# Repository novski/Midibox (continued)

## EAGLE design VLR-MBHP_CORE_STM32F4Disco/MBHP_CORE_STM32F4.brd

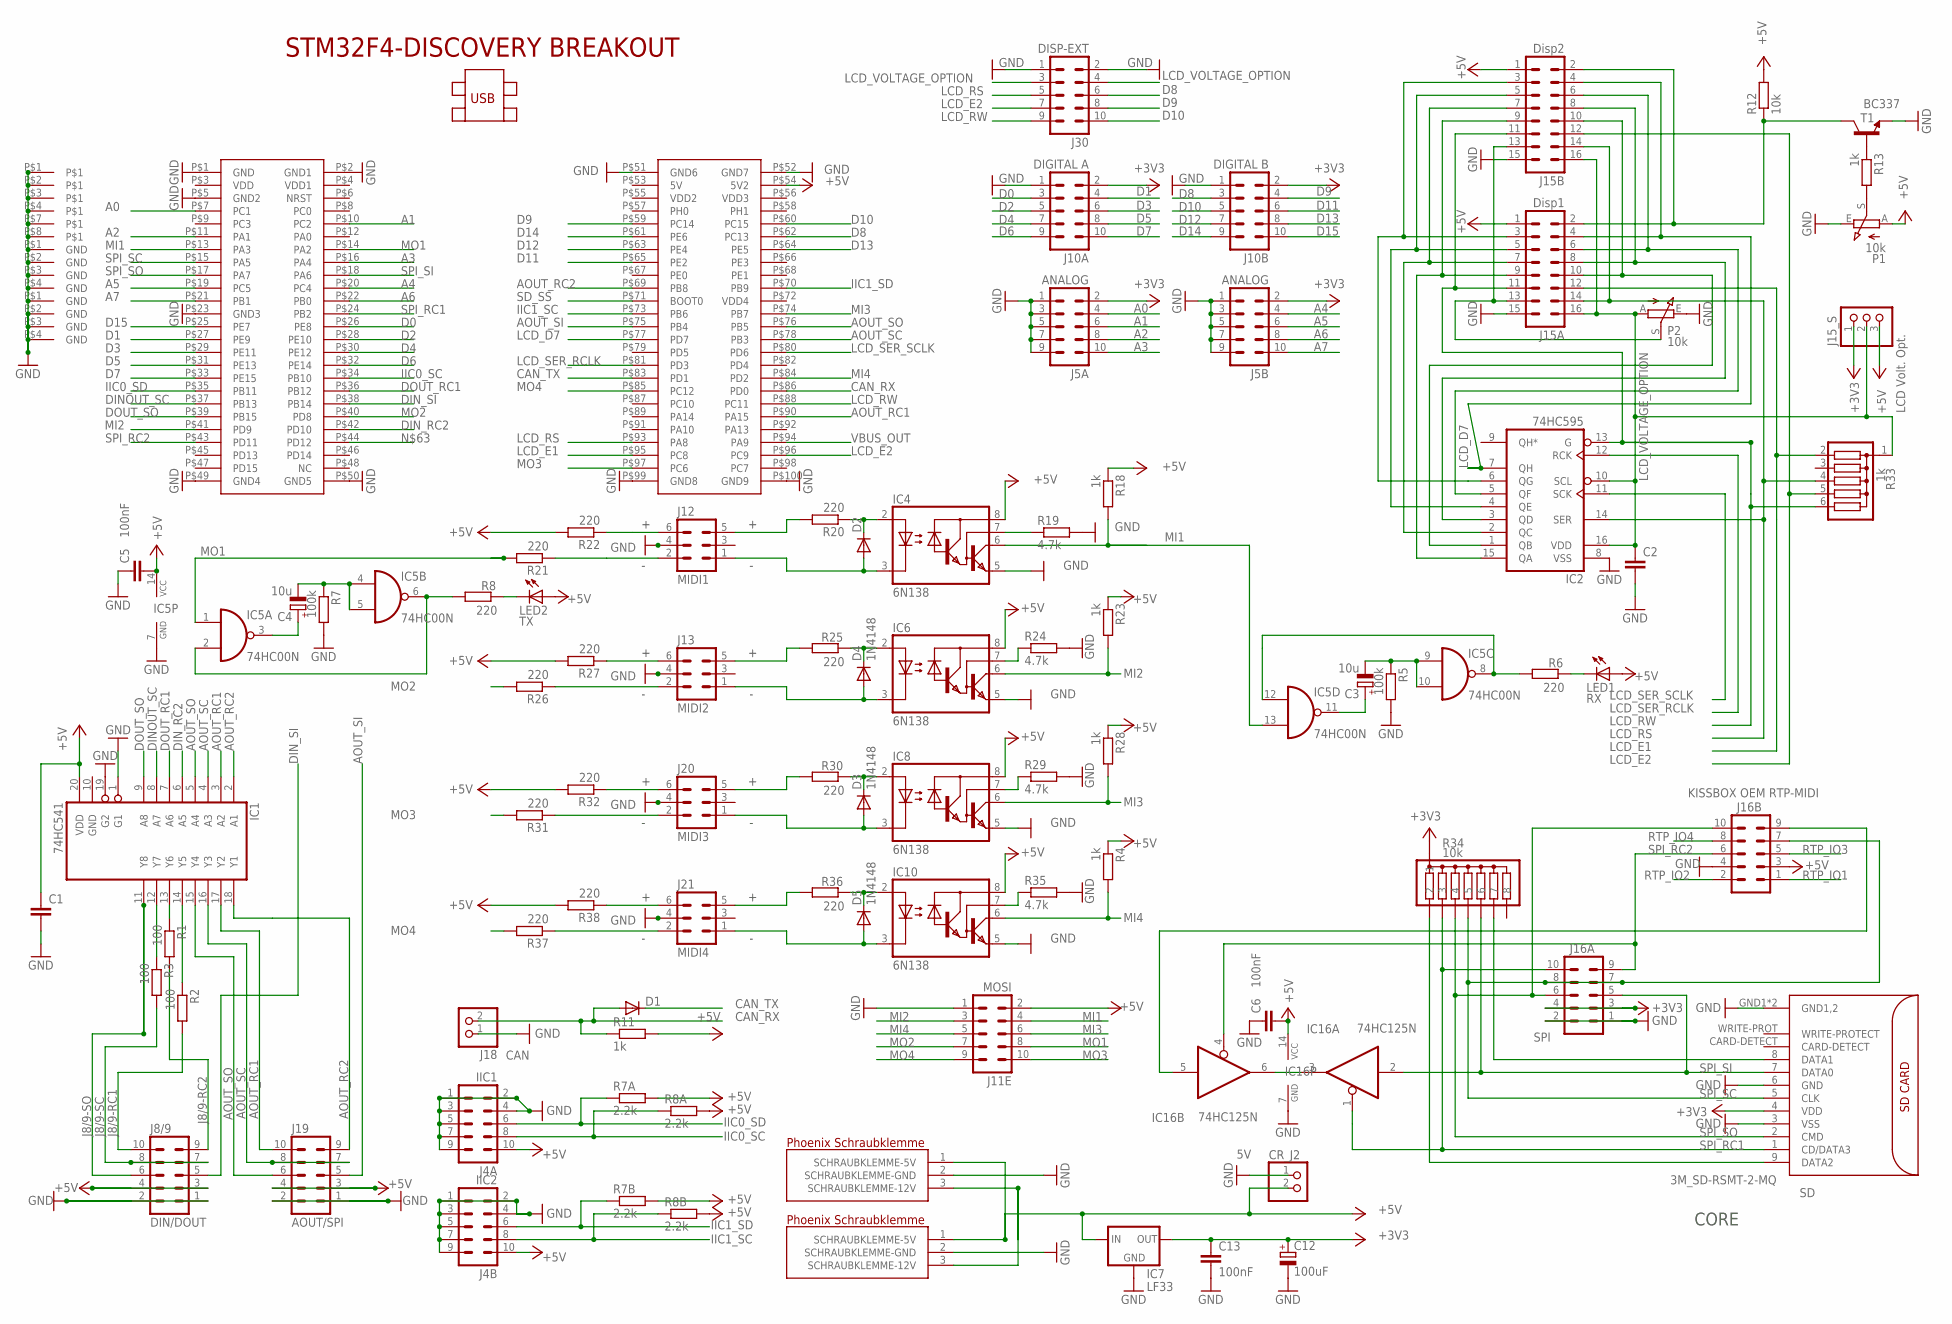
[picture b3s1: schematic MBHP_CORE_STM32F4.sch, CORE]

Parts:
C1, C2: C-EU025-025X050; C025-025X050
C3, C4: 10u; E2,5-6
C5, C6, C13: 100nF; C025-025X050
C12: 100uF; E5-10,5
CR_J2: 5V; 1X02
D1, D3, D4, D5: 1N4148; DO35-7
D2: 1N4148DO35-7; DO35-7
IC1: 74HC541; DIL20
IC2: 74HC595; DIL16
IC4, IC6, IC8, IC10: 6N138; DIL08
IC5: 74HC00N; DIL14
IC7: LF33; TO220
IC16: 74HC125N; DIL14
J1A, J1B: PT-1.5/3; PT-1.5/3-5.0
J4A: IIC1; ML10
J4B: IIC2; ML10
J5A, J5B: ANALOG; ML10
J8/9: DIN/DOUT; ML10
J10A: DIGITAL A; ML10
J10B: DIGITAL B; ML10
J11E: MOSI; ML10
J12: MIDI1; ML6
J13: MIDI2; ML6
J15A: Disp1; ML16
J15B: Disp2; ML16
J15_S: LCD Volt. Opt.; 1X03
J16A: SPI; ML10
J16B: KISSBOX OEM RTP-MIDI; ML10
J18: CAN; 1X02
J19: AOUT/SPI; ML10
J20: MIDI3; ML6
J21: MIDI4; ML6
J30: DISP-EXT; ML10
LED1: RX; LED3MM
LED2: TX; LED3MM
OUTLINE: MIDIBOX_FULL; MIDIBOX14X12
P1, P2: 10k; 6MM_V
R1, R2, R3: 100; 0204/7
R4, R11, R13, R18, R23, R28: 1k; 0204/7
R5, R7: 100k; 0204/7
R6, R8, R20, R21, R22, R25, R26, R27, R30, R31, R32, R36, R37, R38: 220; 0204/7
R7A, R7B, R8A, R8B: 2.2k; 0204/7
R12: 10k; 0204/7
R19, R24, R29, R35: 4.7k; 0204/7
R33: 1k; SIL6
R34: 10k; SIL8
SD: 3M_SD-RSMT-2-MQ
STM32F4DISCOVERY: STM32F4-DISCOVERY
T1: BC337; TO92
U$1, U$2: KEYSTONE_SCREW_TERMINAL

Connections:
+3V3: C12.+, C13.1, IC7.OUT, J5A.2, J5B.2, J10A.2, J10B.2, J15_S.1, J16A.3, J16A.4, R34.1, SD.4 (VDD)
+5V: C1.1, C5.2, C6.2, CR_J2.2, IC1.20 (VDD), IC4.8 (VCC), IC5.14 (VCC), IC6.8 (VCC), IC7.IN, IC8.8 (VCC), IC10.8 (VCC), IC16.14 (VCC), J1A.1 (SCHRAUBKLEMME-5V), J1B.1 (SCHRAUBKLEMME-5V), J4A.10, J4B.10, J8/9.3, J8/9.4, J11E.2, J15A.1, J15B.1, J15_S.3, J16B.3, J19.3, J19.4, LED1.A, LED2.A, P1.A, R4.1, R7A.2, R7B.2, R8A.2, R8B.2, R11.2, R12.2, R18.1, R22.2, R23.1, R27.2, R28.1, R32.2, R38.2, STM32F4DISCOVERY.P$54 (5V2)
+12V1: J1A.3 (SCHRAUBKLEMME-12V), J1B.3 (SCHRAUBKLEMME-12V)
A0: J5A.4, STM32F4DISCOVERY.P$7 (PC1)
A1: J5A.6, STM32F4DISCOVERY.P$10 (PC2)
A2: J5A.8, STM32F4DISCOVERY.P$11 (PA1)
A3: J5A.10, STM32F4DISCOVERY.P$16 (PA4)
A4: J5B.4, STM32F4DISCOVERY.P$20 (PC4)
A5: J5B.6, STM32F4DISCOVERY.P$19 (PC5)
A6: J5B.8, STM32F4DISCOVERY.P$22 (PB0)
A7: J5B.10, STM32F4DISCOVERY.P$21 (PB1)
AOUT_RC1: IC1.3 (A2), IC1.17 (Y2), J19.10, STM32F4DISCOVERY.P$90 (PA15)
AOUT_RC2: IC1.2 (A1), IC1.18 (Y1), J19.9, STM32F4DISCOVERY.P$69 (PB8)
AOUT_SC: IC1.4 (A3), IC1.16 (Y3), J19.7, J19.8, STM32F4DISCOVERY.P$78 (PB3)
AOUT_SI: J19.5, STM32F4DISCOVERY.P$75 (PB4)
AOUT_SO: IC1.5 (A4), IC1.15 (Y4), J19.6, STM32F4DISCOVERY.P$76 (PB5)
CAN_RX: D1.A, J18.2, R11.1, STM32F4DISCOVERY.P$86 (PD0)
CAN_TX: D1.C, STM32F4DISCOVERY.P$83 (PD1)
CR_M1-: D2.A, IC4.3 (C), J12.1
CR_M2+$1: D2.C, IC4.2 (A), R20.1
D0: J10A.3, STM32F4DISCOVERY.P$26 (PE8)
D1: J10A.4, STM32F4DISCOVERY.P$27 (PE9)
D2: J10A.5, STM32F4DISCOVERY.P$28 (PE10)
D3: J10A.6, STM32F4DISCOVERY.P$29 (PE11)
D4: J10A.7, STM32F4DISCOVERY.P$30 (PE12)
D5: J10A.8, STM32F4DISCOVERY.P$31 (PE13)
D6: J10A.9, STM32F4DISCOVERY.P$32 (PE14)
D7: J10A.10, STM32F4DISCOVERY.P$33 (PE15)
D8: J10B.3, J30.6, STM32F4DISCOVERY.P$62 (PC13)
D9: J10B.4, J30.8, STM32F4DISCOVERY.P$59 (PC14)
D10: J10B.5, J30.10, STM32F4DISCOVERY.P$60 (PC15)
D11: J10B.6, STM32F4DISCOVERY.P$65 (PE2)
D12: J10B.7, STM32F4DISCOVERY.P$63 (PE4)
D13: J10B.8, STM32F4DISCOVERY.P$64 (PE5)
D14: J10B.9, STM32F4DISCOVERY.P$61 (PE6)
D15: J10B.10, STM32F4DISCOVERY.P$25 (PE7)
DINOUT_SC: IC1.8 (A7), STM32F4DISCOVERY.P$37 (PB13)
DIN_RC2: IC1.6 (A5), STM32F4DISCOVERY.P$42 (PD10)
DIN_SI: J8/9.5, STM32F4DISCOVERY.P$38 (PB14)
DOUT_RC1: IC1.7 (A6), STM32F4DISCOVERY.P$36 (PB12)
DOUT_SO: IC1.9 (A8), STM32F4DISCOVERY.P$39 (PB15)
GND: C1.2, C2.2, C5.1, C6.1, C12.-, C13.2, CR_J2.1, IC1.1 (G1), IC1.10 (GND), IC1.19 (G2), IC2.8 (VSS), IC4.5 (GND), IC5.7 (GND), IC6.5 (GND), IC7.GND, IC8.5 (GND), IC10.5 (GND), IC16.7 (GND), J1A.2 (SCHRAUBKLEMME-GND), J1B.2 (SCHRAUBKLEMME-GND), J4A.1, J4A.2, J4A.3, J4A.4, J4A.5, J4A.7, J4A.9, J4B.1, J4B.2, J4B.3, J4B.4, J4B.5, J4B.7, J4B.9, J5A.1, J5A.3, J5A.5, J5A.7, J5A.9, J5B.1, J5B.3, J5B.5, J5B.7, J5B.9, J8/9.1, J8/9.2, J10A.1, J10B.1, J11E.1, J12.4, J13.4, J15A.15, J15B.15, J16A.1, J16A.2, J16B.4, J18.1, J19.1, J19.2, J20.4, J21.4, J30.1, J30.2, OUTLINE.P$1, OUTLINE.P$2, OUTLINE.P$3, OUTLINE.P$4, OUTLINE.P$7, OUTLINE.P$8, P1.E, P2.E, R5.2, R7.2, R19.2, R24.2, R29.2, R35.2, SD.3 (VSS), SD.6 (GND), SD.GND1 (GND1,2), SD.GND2 (GND1,2), STM32F4DISCOVERY.P$1 (GND), STM32F4DISCOVERY.P$2 (GND1), STM32F4DISCOVERY.P$5 (GND2), STM32F4DISCOVERY.P$23 (GND3), STM32F4DISCOVERY.P$49 (GND4), STM32F4DISCOVERY.P$50 (GND5), STM32F4DISCOVERY.P$51 (GND6), STM32F4DISCOVERY.P$52 (GND7), STM32F4DISCOVERY.P$99 (GND8), STM32F4DISCOVERY.P$100 (GND9), T1.1 (E), U$1.P$1, U$1.P$2, U$1.P$3, U$1.P$4, U$2.P$1, U$2.P$2, U$2.P$3, U$2.P$4
IIC0_SC: J4A.8, R8A.1, STM32F4DISCOVERY.P$34 (PB10)
IIC0_SD: J4A.6, R7A.1, STM32F4DISCOVERY.P$35 (PB11)
IIC1_SC: J4B.8, R8B.1, STM32F4DISCOVERY.P$73 (PB6)
IIC1_SD: J4B.6, R7B.1, STM32F4DISCOVERY.P$70 (PB9)
J8/9-RC1: J8/9.10, R2.2
J8/9-RC2: J8/9.9, R1.2
J8/9-SC: J8/9.7, J8/9.8, R3.2
J8/9-SO: IC1.11 (Y8), J8/9.6
LCD_D7: IC2.7 (QH), J15A.4, J15B.4, STM32F4DISCOVERY.P$77 (PD7)
LCD_E1: J15A.12, R33.2, STM32F4DISCOVERY.P$95 (PC8)
LCD_E2: J15B.12, J30.7, R33.5, STM32F4DISCOVERY.P$96 (PC9)
LCD_RS: IC2.14 (SER), J15A.14, J15B.14, J30.5, R33.4, STM32F4DISCOVERY.P$93 (PA8)
LCD_RW: IC2.13 (G), J15A.11, J15B.11, J30.9, R33.6, STM32F4DISCOVERY.P$88 (PC11)
LCD_SER_RCLK: IC2.12 (RCK), STM32F4DISCOVERY.P$81 (PD3)
LCD_SER_SCLK: IC2.11 (SCK), STM32F4DISCOVERY.P$80 (PD6)
LCD_VOLTAGE_OPTION: C2.1, IC2.10 (SCL), IC2.16 (VDD), J15A.16, J15B.16, J15_S.2, J30.3, J30.4, P2.A, R33.1
MF_M+ZULEITUNG: J13.5, R25.2
MF_M+ZULEITUNG1: J20.5, R30.2
MF_M+ZULEITUNG2: J21.5, R36.2
MF_M-ZULEITUNG: D4.A, IC6.3 (C), J13.1
MF_M-ZULEITUNG1: D3.A, IC8.3 (C), J20.1
MF_M-ZULEITUNG2: D5.A, IC10.3 (C), J21.1
MI1: IC4.6 (VO), IC5.13 (I1), J11E.4, R18.2, STM32F4DISCOVERY.P$13 (PA3)
MI2: IC6.6 (VO), J11E.3, R23.2, STM32F4DISCOVERY.P$41 (PD9)
MI3: IC8.6 (VO), J11E.6, R28.2, STM32F4DISCOVERY.P$74 (PB7)
MI4: IC10.6 (VO), J11E.5, R4.2, STM32F4DISCOVERY.P$84 (PD2)
MO1: IC5.1 (I0), J11E.8, R21.2, STM32F4DISCOVERY.P$14 (PA2)
MO2: J11E.7, R26.2, STM32F4DISCOVERY.P$40 (PD8)
MO3: J11E.10, R31.2, STM32F4DISCOVERY.P$97 (PC6)
MO4: J11E.9, R37.2, STM32F4DISCOVERY.P$85 (PC12)
unnamed: IC2.6 (QG), J15A.3, J15B.3
unnamed: IC2.5 (QF), J15A.6, J15B.6
unnamed: IC2.4 (QE), J15A.5, J15B.5
unnamed: IC2.3 (QD), J15A.8, J15B.8
unnamed: R34.2, SD.9 (DATA2)
unnamed: IC16.5 (I), J16B.9
unnamed: R34.7, SD.8 (DATA1)
unnamed: IC2.2 (QC), J15A.7, J15B.7
unnamed: IC2.1 (QB), J15A.10, J15B.10
unnamed: IC2.15 (QA), J15A.9, J15B.9
unnamed: IC4.7 (VB), R19.1
unnamed: J15A.13, J15B.13, P2.S
unnamed: IC16.3 (O), IC16.6 (O)
unnamed: P1.S, R13.2
unnamed: R13.1, T1.2 (B)
unnamed: J12.6, R22.1
unnamed: J15A.2, J15B.2, R12.1, T1.3 (C)
unnamed: D4.C, IC6.2 (A), R25.1
unnamed: J12.5, R20.2
unnamed: C3.-, IC5.9 (I0), IC5.10 (I1), R5.1
unnamed: C3.+, IC5.11 (O)
unnamed: IC5.8 (O), IC5.12 (I0), R6.2
unnamed: J13.6, R27.1
unnamed: J13.2, R26.1
unnamed: LED1.K (C), R6.1
unnamed: D3.C, IC8.2 (A), R30.1
unnamed: IC8.7 (VB), R29.1
unnamed: J20.6, R32.1
unnamed: J20.2, R31.1
unnamed: D5.C, IC10.2 (A), R36.1
unnamed: IC10.7 (VB), R35.1
unnamed: J21.6, R38.1
unnamed: J21.2, R37.1
unnamed: IC5.4 (I0), IC5.5 (I1)
unnamed: C4.-, R7.1
unnamed: C4.+, IC5.3 (O)
unnamed: IC5.2 (I1), IC5.6 (O), R8.2
unnamed: LED2.K (C), R8.1
unnamed: J12.2, R21.1
unnamed: IC6.7 (VB), R24.1
RC-I-: IC1.14 (Y5), R2.1
RC-O-: IC1.13 (Y6), R1.1
RTP_IO1: J16B.1
RTP_IO2: J16B.2
RTP_IO3: J16B.5
RTP_IO4: J16B.8
SC-: IC1.12 (Y7), R3.1
SD_SS: STM32F4DISCOVERY.P$71 (BOOT0)
SPI_RC1: IC16.1 (OE), J16A.10, R34.3, SD.1 (CD/DATA3), STM32F4DISCOVERY.P$24 (PB2)
SPI_RC2: IC16.4 (OE), J16A.9, J16B.6, STM32F4DISCOVERY.P$43 (PD11)
SPI_SC: J16A.7, J16A.8, J16B.7, R34.5, SD.5 (CLK), STM32F4DISCOVERY.P$15 (PA5)
SPI_SI: IC16.2 (I), J16A.5, R34.6, SD.7 (DATA0), STM32F4DISCOVERY.P$18 (PA6)
SPI_SO: J16A.6, J16B.10, R34.4, SD.2 (CMD), STM32F4DISCOVERY.P$17 (PA7)
VBUS_OUT: STM32F4DISCOVERY.P$94 (PA9)

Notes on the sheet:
CORE

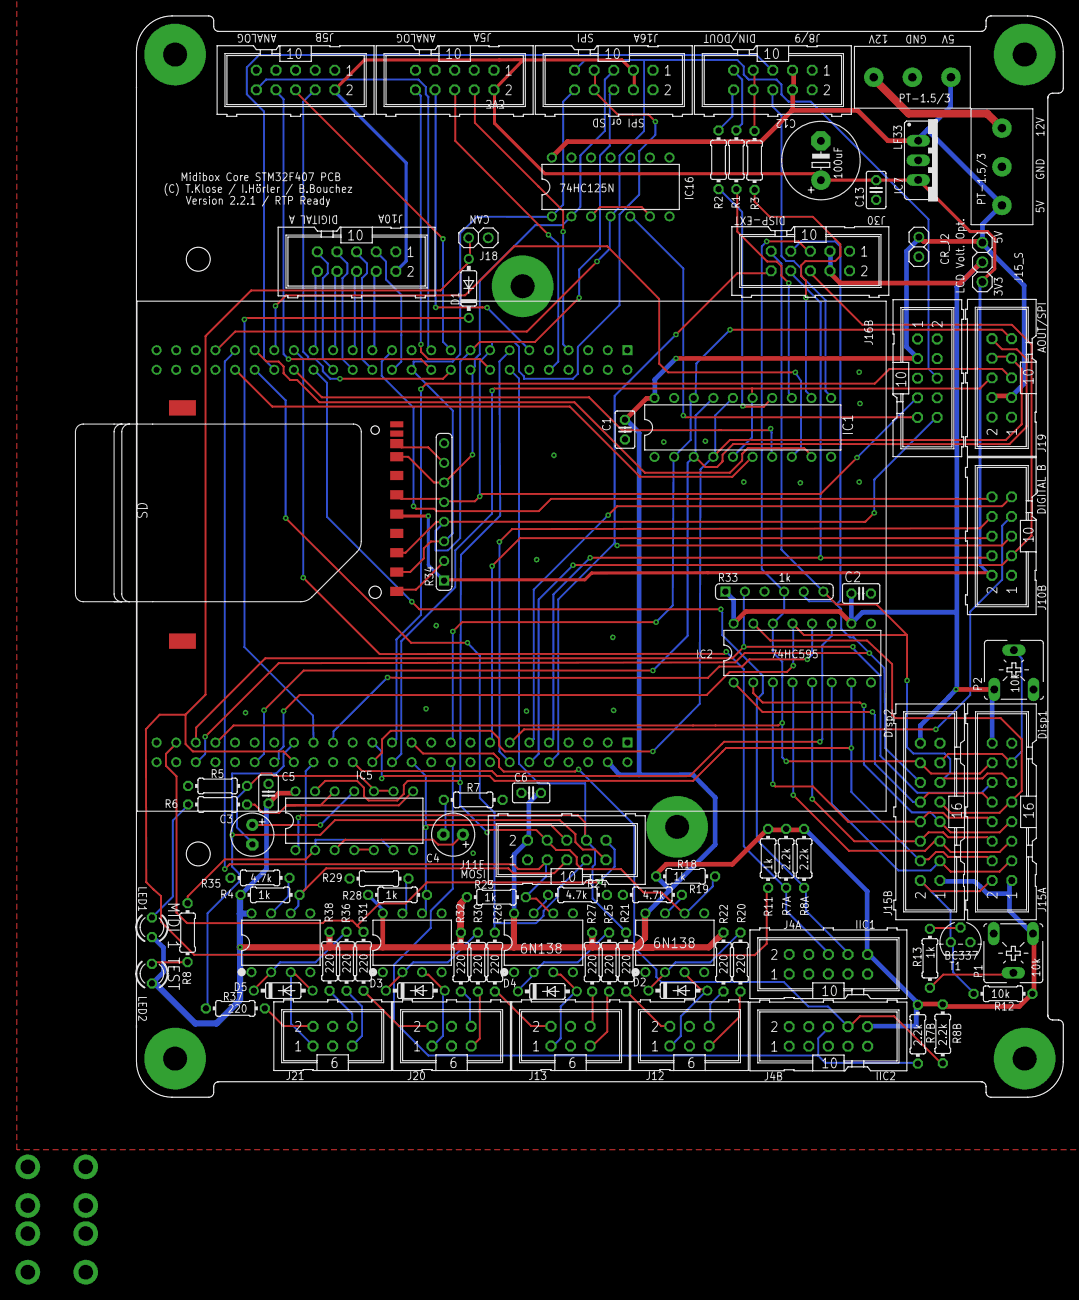
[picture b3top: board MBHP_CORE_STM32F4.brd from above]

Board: 2 copper layers, 120.0 x 140.0 mm, 93 parts (1 on the bottom side), 120 nets.

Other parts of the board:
U$6, U$7: VLRLAB

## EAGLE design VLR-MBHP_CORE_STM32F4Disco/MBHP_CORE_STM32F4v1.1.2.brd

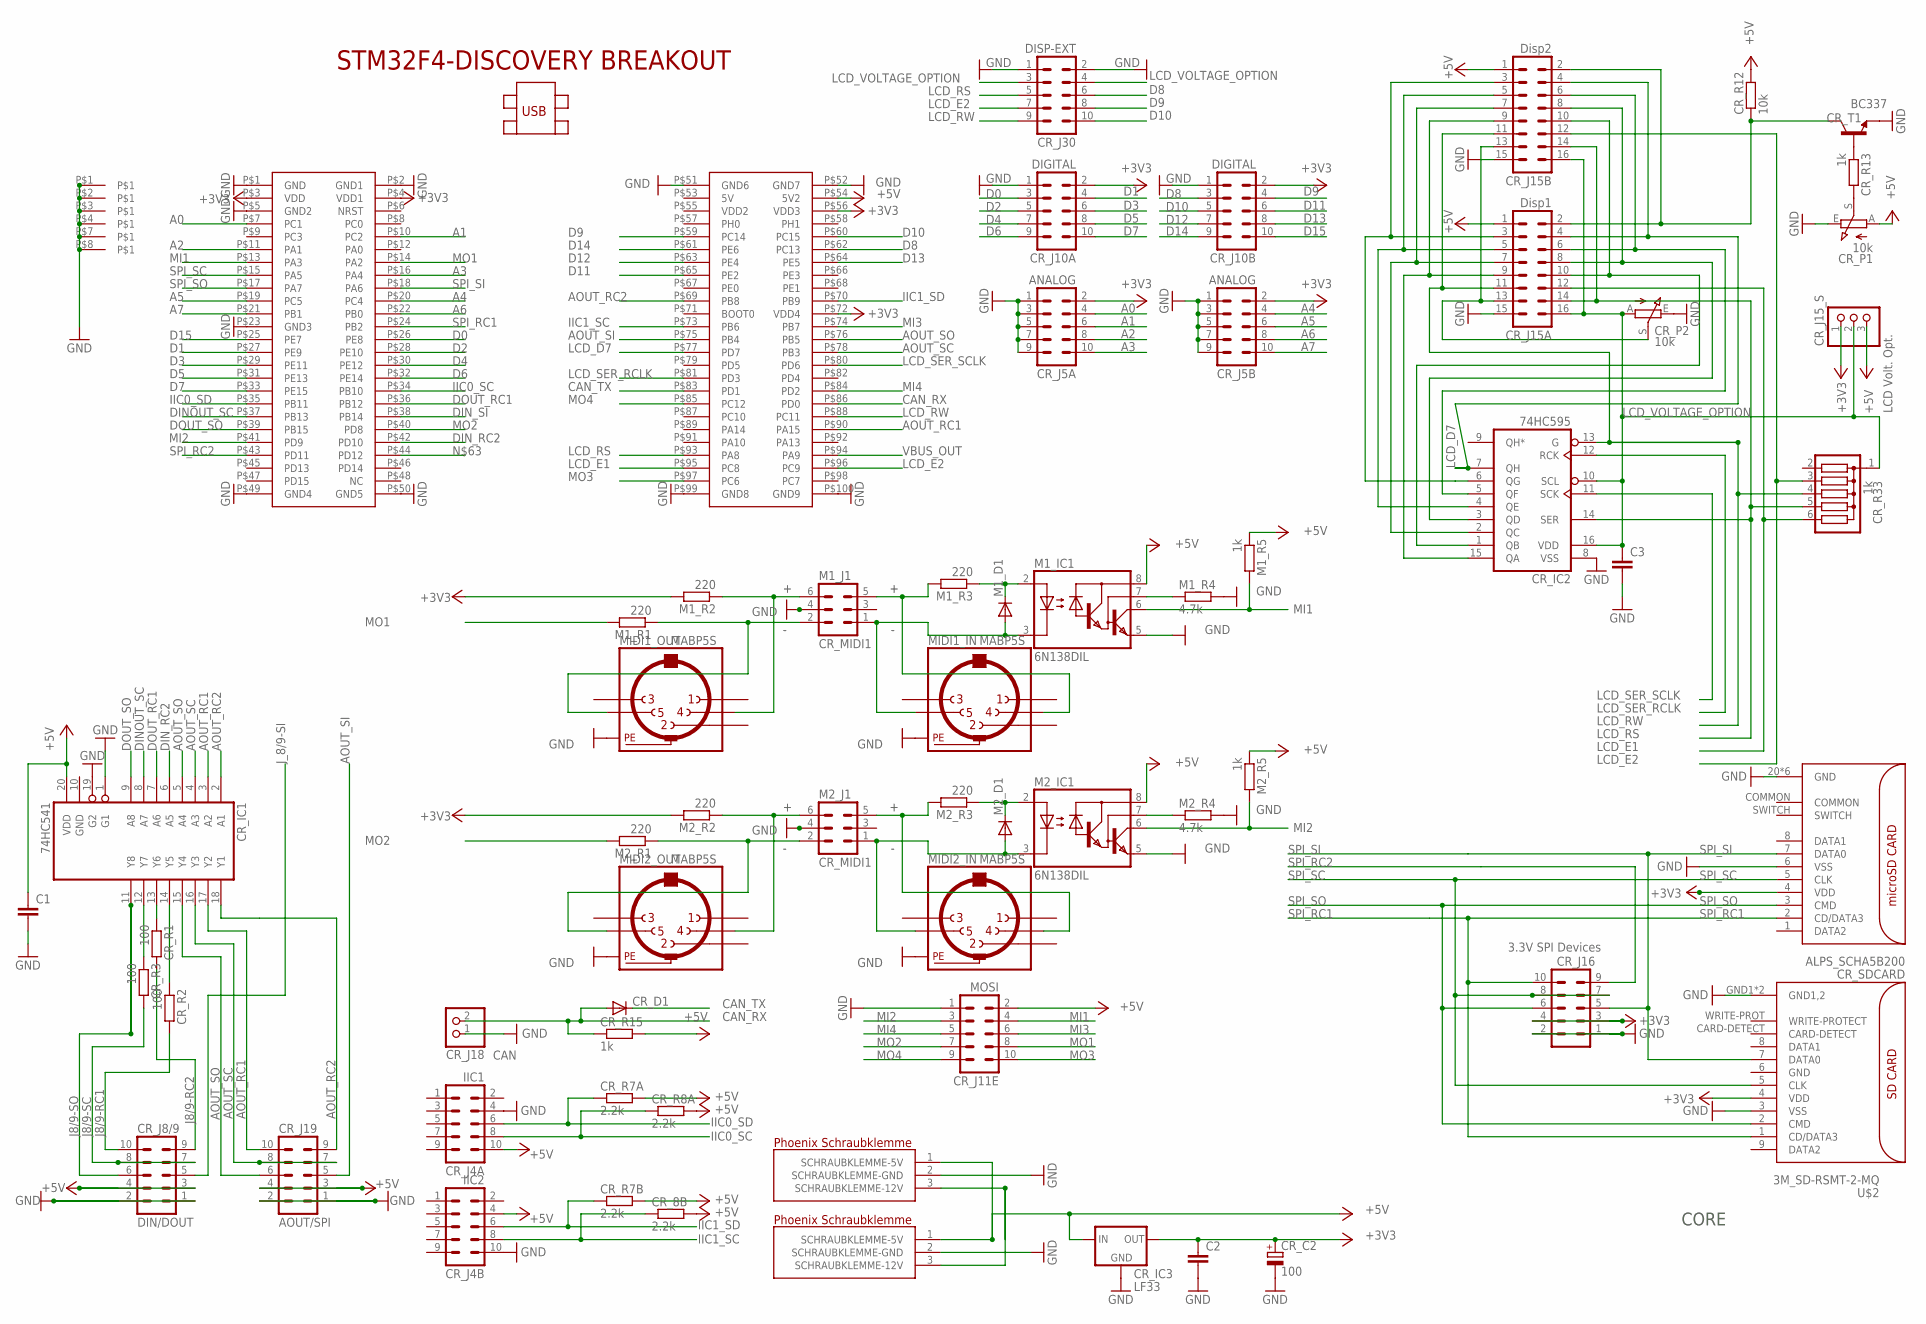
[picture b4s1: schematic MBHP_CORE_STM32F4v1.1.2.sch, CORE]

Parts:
C1, C2, C3: C-EU025-025X050; C025-025X050
CR_8B: 2.2k; 0204/7
CR_C2: 100; E5-10,5
CR_D1: 1N4148; DO35-7
CR_IC1: 74HC541; DIL20
CR_IC2: 74HC595; DIL16
CR_IC3: LF33; TO220
CR_J4A: IIC1; ML10
CR_J4B: IIC2; ML10
CR_J5A, CR_J5B: ANALOG; ML10
CR_J8/9: DIN/DOUT; ML10
CR_J10A, CR_J10B: DIGITAL; ML10
CR_J11E: MOSI; ML10
CR_J15A: Disp1; ML16
CR_J15B: Disp2; ML16
CR_J15_S: LCD Volt. Opt.; 1X03
CR_J16: 3.3V SPI Devices; ML10
CR_J18: CAN; 1X02
CR_J19: AOUT/SPI; ML10
CR_J30: DISP-EXT; ML10
CR_P1, CR_P2: 10k; 6MM_V
CR_R1, CR_R2, CR_R3: 100; 0204/7
CR_R7A, CR_R7B, CR_R8A: 2.2k; 0204/7
CR_R12: 10k; 0204/7
CR_R13, CR_R15: 1k; 0204/7
CR_R33: 1k; SIL6
CR_SDCARD: ALPS_SCHA5B200; ALPS_SCHA5B0200_MICRO_SD_PUSHPUSH
CR_T1: BC337; TO92
KLEMME3, KLEMME4: PT-1.5/3; PT-1.5/3-5.0
M1_D1, M2_D1: 1N4148DO35-7; DO35-7
M1_IC1, M2_IC1: 6N138DIL; DIL08
M1_J1, M2_J1: CR_MIDI1; ML6
M1_R1, M1_R2, M1_R3, M2_R1, M2_R2, M2_R3: 220; 0204/7
M1_R4, M2_R4: 4.7k; 0204/7
M1_R5, M2_R5: 1k; 0204/7
MIDI1_IN, MIDI1_OUT, MIDI2_IN, MIDI2_OUT: MABP5S
OUTLINE: MIDIBOX_FULL; MIDIBOX14X12
STM32F4DISCOVERY: STM32F4-DISCOVERY
U$2: 3M_SD-RSMT-2-MQ

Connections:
+3V3: C2.1, CR_C2.+, CR_IC3.OUT, CR_J5A.2, CR_J5B.2, CR_J10A.2, CR_J10B.2, CR_J15_S.1, CR_J16.3, CR_J16.4, CR_SDCARD.4 (VDD), M1_R2.2, M2_R2.2, STM32F4DISCOVERY.P$3 (VDD), STM32F4DISCOVERY.P$4 (VDD1), STM32F4DISCOVERY.P$56 (VDD3), STM32F4DISCOVERY.P$72 (VDD4), U$2.4 (VDD)
+5V: C1.1, CR_8B.2, CR_IC1.20 (VDD), CR_IC3.IN, CR_J4A.10, CR_J4B.4, CR_J8/9.3, CR_J8/9.4, CR_J11E.2, CR_J15A.1, CR_J15B.1, CR_J15_S.3, CR_J19.3, CR_J19.4, CR_P1.A, CR_R7A.2, CR_R7B.2, CR_R8A.2, CR_R12.2, CR_R15.2, KLEMME3.1 (SCHRAUBKLEMME-5V), KLEMME4.1 (SCHRAUBKLEMME-5V), M1_IC1.8 (VCC), M1_R5.1, M2_IC1.8 (VCC), M2_R5.1, STM32F4DISCOVERY.P$54 (5V2)
+12V1: KLEMME3.3 (SCHRAUBKLEMME-12V), KLEMME4.3 (SCHRAUBKLEMME-12V)
A0: CR_J5A.4, STM32F4DISCOVERY.P$7 (PC1)
A1: CR_J5A.6, STM32F4DISCOVERY.P$10 (PC2)
A2: CR_J5A.8, STM32F4DISCOVERY.P$11 (PA1)
A3: CR_J5A.10, STM32F4DISCOVERY.P$16 (PA4)
A4: CR_J5B.4, STM32F4DISCOVERY.P$20 (PC4)
A5: CR_J5B.6, STM32F4DISCOVERY.P$19 (PC5)
A6: CR_J5B.8, STM32F4DISCOVERY.P$22 (PB0)
A7: CR_J5B.10, STM32F4DISCOVERY.P$21 (PB1)
AOUT_RC1: CR_IC1.3 (A2), CR_IC1.17 (Y2), CR_J19.10, STM32F4DISCOVERY.P$90 (PA15)
AOUT_RC2: CR_IC1.2 (A1), CR_IC1.18 (Y1), CR_J19.9, STM32F4DISCOVERY.P$69 (PB8)
AOUT_SC: CR_IC1.4 (A3), CR_IC1.16 (Y3), CR_J19.7, CR_J19.8, STM32F4DISCOVERY.P$78 (PB3)
AOUT_SI: CR_J19.5, STM32F4DISCOVERY.P$75 (PB4)
AOUT_SO: CR_IC1.5 (A4), CR_IC1.15 (Y4), CR_J19.6, STM32F4DISCOVERY.P$76 (PB5)
CAN_RX: CR_D1.A, CR_J18.2, CR_R15.1, STM32F4DISCOVERY.P$86 (PD0)
CAN_TX: CR_D1.C, STM32F4DISCOVERY.P$83 (PD1)
D0: CR_J10A.3, STM32F4DISCOVERY.P$26 (PE8)
D1: CR_J10A.4, STM32F4DISCOVERY.P$27 (PE9)
D2: CR_J10A.5, STM32F4DISCOVERY.P$28 (PE10)
D3: CR_J10A.6, STM32F4DISCOVERY.P$29 (PE11)
D4: CR_J10A.7, STM32F4DISCOVERY.P$30 (PE12)
D5: CR_J10A.8, STM32F4DISCOVERY.P$31 (PE13)
D6: CR_J10A.9, STM32F4DISCOVERY.P$32 (PE14)
D7: CR_J10A.10, STM32F4DISCOVERY.P$33 (PE15)
D8: CR_J10B.3, CR_J30.6, STM32F4DISCOVERY.P$62 (PC13)
D9: CR_J10B.4, CR_J30.8, STM32F4DISCOVERY.P$59 (PC14)
D10: CR_J10B.5, CR_J30.10, STM32F4DISCOVERY.P$60 (PC15)
D11: CR_J10B.6, STM32F4DISCOVERY.P$65 (PE2)
D12: CR_J10B.7, STM32F4DISCOVERY.P$63 (PE4)
D13: CR_J10B.8, STM32F4DISCOVERY.P$64 (PE5)
D14: CR_J10B.9, STM32F4DISCOVERY.P$61 (PE6)
D15: CR_J10B.10, STM32F4DISCOVERY.P$25 (PE7)
DINOUT_SC: CR_IC1.8 (A7), STM32F4DISCOVERY.P$37 (PB13)
DIN_RC2: CR_IC1.6 (A5), STM32F4DISCOVERY.P$42 (PD10)
DIN_SI: STM32F4DISCOVERY.P$38 (PB14)
DOUT_RC1: CR_IC1.7 (A6), STM32F4DISCOVERY.P$36 (PB12)
DOUT_SO: CR_IC1.9 (A8), STM32F4DISCOVERY.P$39 (PB15)
GND: C1.2, C2.2, C3.2, CR_C2.-, CR_IC1.1 (G1), CR_IC1.10 (GND), CR_IC1.19 (G2), CR_IC2.8 (VSS), CR_IC3.GND, CR_J4A.4, CR_J4B.10, CR_J5A.1, CR_J5A.3, CR_J5A.5, CR_J5A.7, CR_J5A.9, CR_J5B.1, CR_J5B.3, CR_J5B.5, CR_J5B.7, CR_J5B.9, CR_J8/9.1, CR_J8/9.2, CR_J10A.1, CR_J10B.1, CR_J11E.1, CR_J15A.15, CR_J15B.15, CR_J16.1, CR_J16.2, CR_J18.1, CR_J19.1, CR_J19.2, CR_J30.1, CR_J30.2, CR_P1.E, CR_P2.E, CR_SDCARD.6 (VSS), CR_SDCARD.20 (GND), CR_SDCARD.21 (GND), CR_SDCARD.22 (GND), CR_SDCARD.23 (GND), CR_SDCARD.24 (GND), CR_SDCARD.25 (GND), CR_T1.1 (E), KLEMME3.2 (SCHRAUBKLEMME-GND), KLEMME4.2 (SCHRAUBKLEMME-GND), M1_IC1.5 (GND), M1_J1.4, M1_R4.2, M2_IC1.5 (GND), M2_J1.4, M2_R4.2, MIDI1_IN.PE, MIDI1_IN.PE@ (PE), MIDI1_OUT.PE, MIDI1_OUT.PE@ (PE), MIDI2_IN.PE, MIDI2_IN.PE@ (PE), MIDI2_OUT.PE, MIDI2_OUT.PE@ (PE), OUTLINE.P$1, OUTLINE.P$2, OUTLINE.P$3, OUTLINE.P$4, OUTLINE.P$7, OUTLINE.P$8, STM32F4DISCOVERY.P$1 (GND), STM32F4DISCOVERY.P$2 (GND1), STM32F4DISCOVERY.P$5 (GND2), STM32F4DISCOVERY.P$23 (GND3), STM32F4DISCOVERY.P$49 (GND4), STM32F4DISCOVERY.P$50 (GND5), STM32F4DISCOVERY.P$51 (GND6), STM32F4DISCOVERY.P$52 (GND7), STM32F4DISCOVERY.P$99 (GND8), STM32F4DISCOVERY.P$100 (GND9), U$2.3 (VSS), U$2.GND1 (GND1,2), U$2.GND2 (GND1,2)
IIC0_SC: CR_J4A.8, CR_R8A.1, STM32F4DISCOVERY.P$34 (PB10)
IIC0_SD: CR_J4A.6, CR_R7A.1, STM32F4DISCOVERY.P$35 (PB11)
IIC1_SC: CR_8B.1, CR_J4B.8, STM32F4DISCOVERY.P$73 (PB6)
IIC1_SD: CR_J4B.6, CR_R7B.1, STM32F4DISCOVERY.P$70 (PB9)
J8/9-RC1: CR_J8/9.10, CR_R2.2
J8/9-RC2: CR_J8/9.9, CR_R1.2
J8/9-SC: CR_J8/9.7, CR_J8/9.8, CR_R3.2
J8/9-SO: CR_IC1.11 (Y8), CR_J8/9.6
J_8/9-SI: CR_J8/9.5
LCD_D7: CR_IC2.7 (QH), CR_J15A.4, CR_J15B.4, STM32F4DISCOVERY.P$77 (PD7)
LCD_E1: CR_J15A.12, CR_R33.6, STM32F4DISCOVERY.P$95 (PC8)
LCD_E2: CR_J15B.12, CR_J30.7, CR_R33.3, STM32F4DISCOVERY.P$96 (PC9)
LCD_RS: CR_IC2.14 (SER), CR_J15A.14, CR_J15B.14, CR_J30.5, CR_R33.5, STM32F4DISCOVERY.P$93 (PA8)
LCD_RW: CR_IC2.13 (G), CR_J15A.11, CR_J15B.11, CR_J30.9, CR_R33.4, STM32F4DISCOVERY.P$88 (PC11)
LCD_SER_RCLK: CR_IC2.12 (RCK), STM32F4DISCOVERY.P$81 (PD3)
LCD_SER_SCLK: CR_IC2.11 (SCK), STM32F4DISCOVERY.P$80 (PD6)
LCD_VOLTAGE_OPTION: C3.1, CR_IC2.10 (SCL), CR_IC2.16 (VDD), CR_J15A.16, CR_J15B.16, CR_J15_S.2, CR_J30.3, CR_J30.4, CR_P2.A, CR_R33.1
M1_R4: M1_IC1.7 (VB), M1_R4.1
M1_RX+: M1_J1.5, M1_R3.2, MIDI1_IN.4
M1_RX+D1: M1_D1.C, M1_IC1.2 (A), M1_R3.1
M1_RX-: M1_D1.A, M1_IC1.3 (C), M1_J1.1, MIDI1_IN.5
M1_TX+: M1_J1.6, M1_R2.1, MIDI1_OUT.4
M1_TX-: M1_J1.2, M1_R1.1, MIDI1_OUT.5
M2_R4: M2_IC1.7 (VB), M2_R4.1
M2_RX+: M2_J1.5, M2_R3.2, MIDI2_IN.4
M2_RX+D1: M2_D1.C, M2_IC1.2 (A), M2_R3.1
M2_RX-: M2_D1.A, M2_IC1.3 (C), M2_J1.1, MIDI2_IN.5
M2_TX+: M2_J1.6, M2_R2.1, MIDI2_OUT.4
M2_TX-: M2_J1.2, M2_R1.1, MIDI2_OUT.5
MI1: CR_J11E.4, M1_IC1.6 (VO), M1_R5.2, STM32F4DISCOVERY.P$13 (PA3)
MI2: CR_J11E.3, M2_IC1.6 (VO), M2_R5.2, STM32F4DISCOVERY.P$41 (PD9)
MI3: CR_J11E.6, STM32F4DISCOVERY.P$74 (PB7)
MI4: CR_J11E.5, STM32F4DISCOVERY.P$84 (PD2)
MO1: CR_J11E.8, M1_R1.2, STM32F4DISCOVERY.P$14 (PA2)
MO2: CR_J11E.7, M2_R1.2, STM32F4DISCOVERY.P$40 (PD8)
MO3: CR_J11E.10, STM32F4DISCOVERY.P$97 (PC6)
MO4: CR_J11E.9, STM32F4DISCOVERY.P$85 (PC12)
unnamed: CR_IC2.6 (QG), CR_J15A.3, CR_J15B.3
unnamed: CR_IC2.5 (QF), CR_J15A.6, CR_J15B.6
unnamed: CR_IC2.4 (QE), CR_J15A.5, CR_J15B.5
unnamed: CR_IC2.3 (QD), CR_J15A.8, CR_J15B.8
unnamed: CR_IC2.2 (QC), CR_J15A.7, CR_J15B.7
unnamed: CR_IC2.1 (QB), CR_J15A.10, CR_J15B.10
unnamed: CR_IC2.15 (QA), CR_J15A.9, CR_J15B.9
unnamed: CR_J15A.13, CR_J15B.13, CR_P2.S
unnamed: CR_P1.S, CR_R13.2
unnamed: CR_R13.1, CR_T1.2 (B)
unnamed: CR_J15A.2, CR_J15B.2, CR_R12.1, CR_T1.3 (C)
RC-I-: CR_IC1.14 (Y5), CR_R2.1
RC-O-: CR_IC1.13 (Y6), CR_R1.1
SC-: CR_IC1.12 (Y7), CR_R3.1
SPI_RC1: CR_J16.10, CR_SDCARD.2 (CD/DATA3), STM32F4DISCOVERY.P$24 (PB2), U$2.1 (CD/DATA3)
SPI_RC2: CR_J16.9, STM32F4DISCOVERY.P$43 (PD11)
SPI_SC: CR_J16.7, CR_J16.8, CR_SDCARD.5 (CLK), STM32F4DISCOVERY.P$15 (PA5), U$2.5 (CLK)
SPI_SI: CR_J16.5, CR_SDCARD.7 (DATA0), STM32F4DISCOVERY.P$18 (PA6), U$2.7 (DATA0)
SPI_SO: CR_J16.6, CR_SDCARD.3 (CMD), STM32F4DISCOVERY.P$17 (PA7), U$2.2 (CMD)
VBUS_OUT: STM32F4DISCOVERY.P$94 (PA9)

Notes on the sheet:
CORE

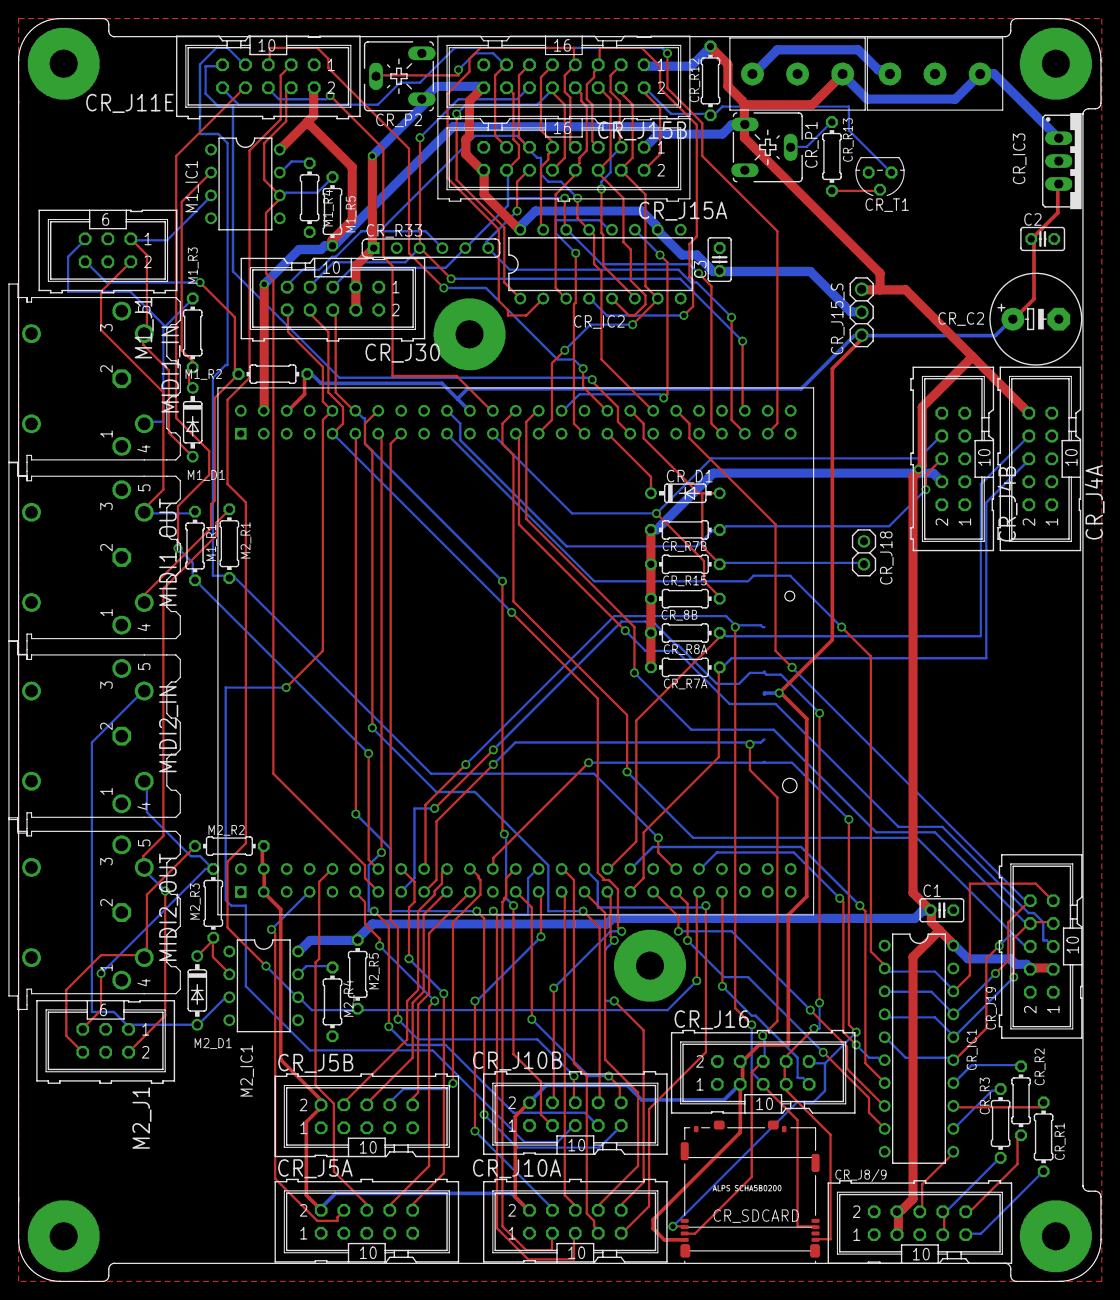
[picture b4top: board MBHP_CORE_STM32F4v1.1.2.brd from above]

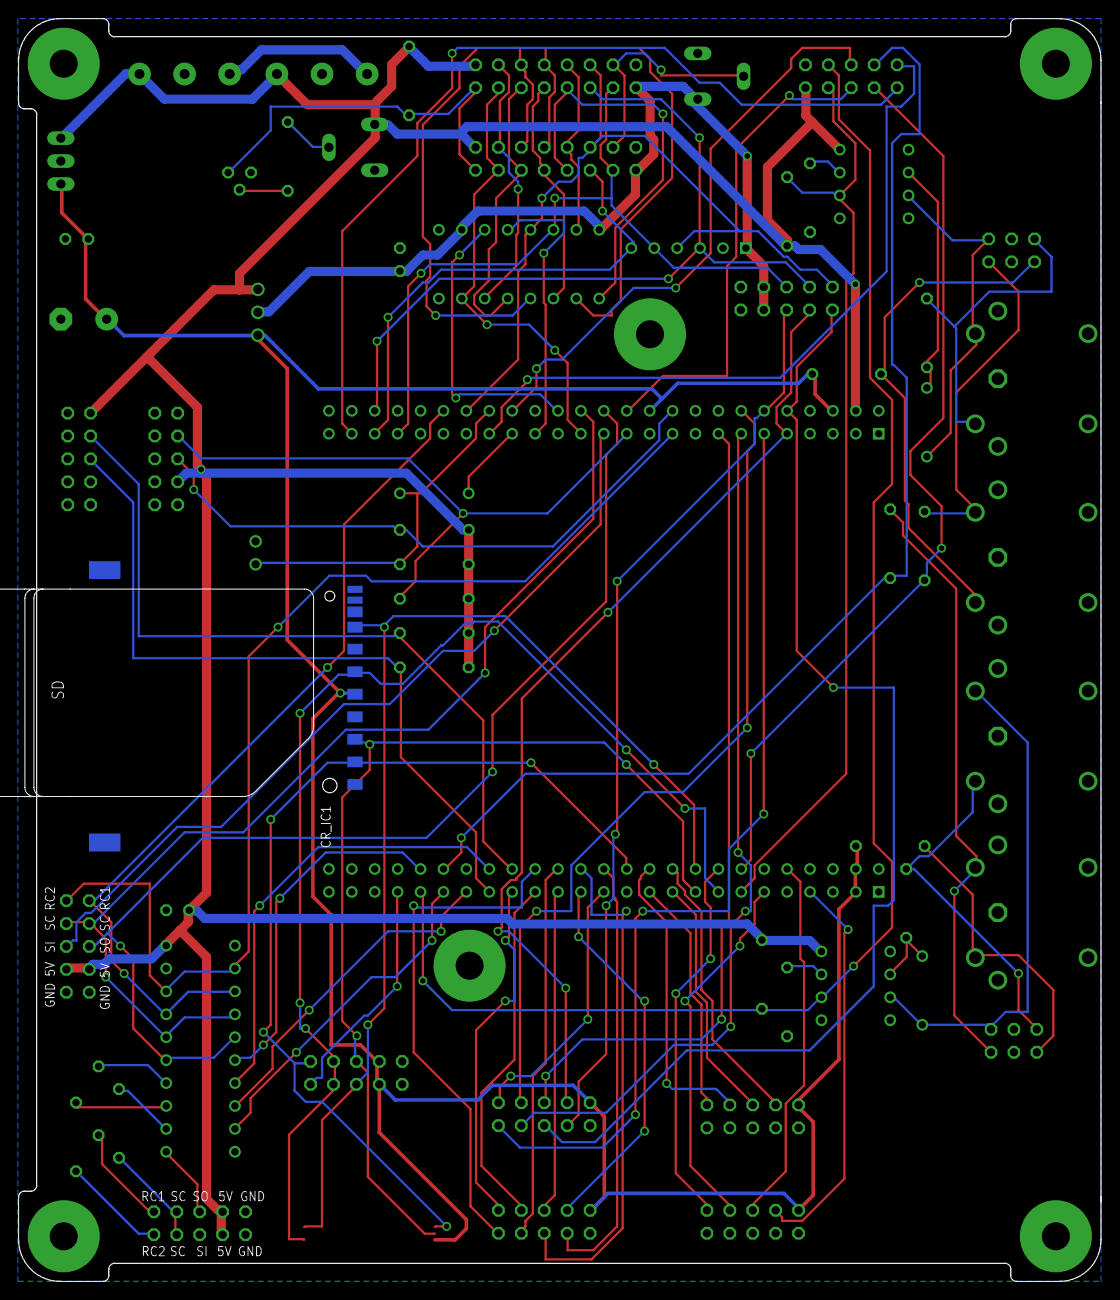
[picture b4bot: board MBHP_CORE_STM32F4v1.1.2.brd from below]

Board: 2 copper layers, 120.0 x 140.0 mm, 67 parts (3 on the bottom side), 94 nets.

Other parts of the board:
U$1, U$5: CORE_LPC17
U$6, U$7: VLRLAB

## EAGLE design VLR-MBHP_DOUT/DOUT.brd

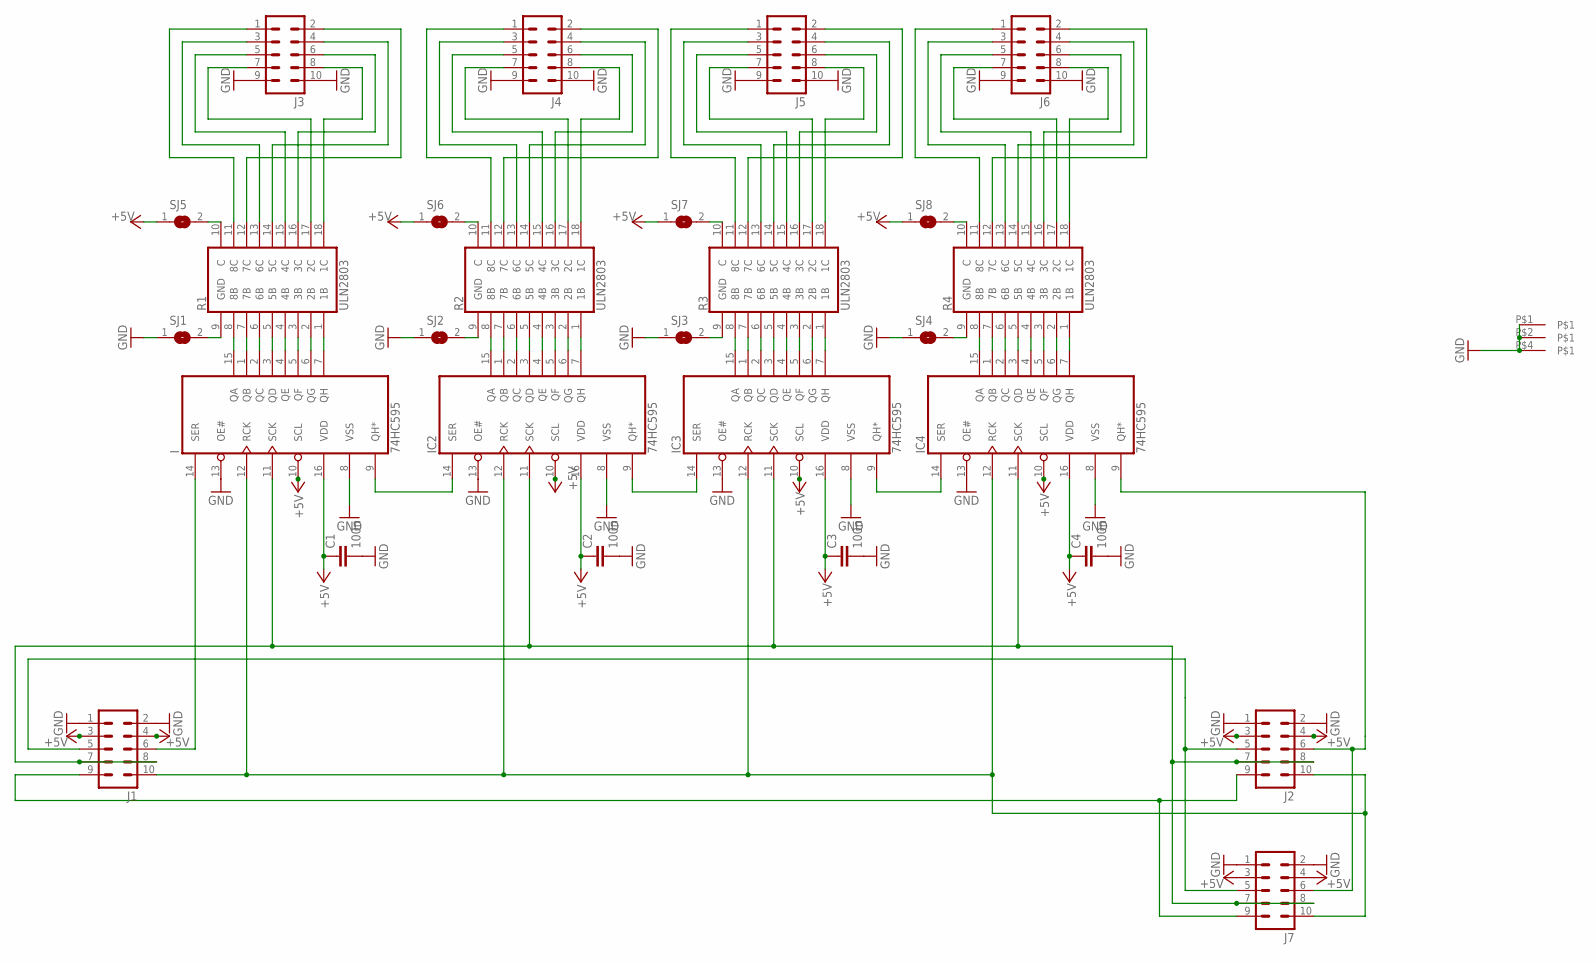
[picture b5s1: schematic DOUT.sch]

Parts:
C1, C2, C3, C4: 100n; C025-025X050
I: 74HC595; DIL16
IC2, IC3, IC4: 74HC595; DIL16
J1, J2, J3, J4, J5, J6, J7: ML10
R1, R2, R3, R4: ULN2803; DIL18
SJ1, SJ2, SJ3, SJ4, SJ5, SJ6, SJ7, SJ8: SJ
U$7: MIDIBOX_HALF; MIDIBOX14X6

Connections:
+5V: C1.1, C2.1, C3.1, C4.1, I.10 (SCL), I.16 (VDD), IC2.10 (SCL), IC2.16 (VDD), IC3.10 (SCL), IC3.16 (VDD), IC4.10 (SCL), IC4.16 (VDD), J1.3, J1.4, J2.3, J2.4, J7.3, J7.4, SJ5.1, SJ6.1, SJ7.1, SJ8.1
GND: C1.2, C2.2, C3.2, C4.2, I.8 (VSS), I.13 (OE#), IC2.8 (VSS), IC2.13 (OE#), IC3.8 (VSS), IC3.13 (OE#), IC4.8 (VSS), IC4.13 (OE#), J1.1, J1.2, J2.1, J2.2, J3.9, J3.10, J4.9, J4.10, J5.9, J5.10, J6.9, J6.10, J7.1, J7.2, SJ1.1, SJ2.1, SJ3.1, SJ4.1, U$7.P$1, U$7.P$2, U$7.P$4
unnamed: J3.1, R1.11 (8C)
unnamed: J3.2, R1.12 (7C)
unnamed: I.6 (QG), R1.2 (2B)
unnamed: I.5 (QF), R1.3 (3B)
unnamed: I.4 (QE), R1.4 (4B)
unnamed: I.3 (QD), R1.5 (5B)
unnamed: I.2 (QC), R1.6 (6B)
unnamed: I.1 (QB), R1.7 (7B)
unnamed: I.15 (QA), R1.8 (8B)
unnamed: I.7 (QH), R1.1 (1B)
unnamed: IC2.6 (QG), R2.2 (2B)
unnamed: IC2.5 (QF), R2.3 (3B)
unnamed: IC2.4 (QE), R2.4 (4B)
unnamed: IC2.3 (QD), R2.5 (5B)
unnamed: IC2.2 (QC), R2.6 (6B)
unnamed: IC2.1 (QB), R2.7 (7B)
unnamed: IC2.15 (QA), R2.8 (8B)
unnamed: IC2.7 (QH), R2.1 (1B)
unnamed: IC3.6 (QG), R3.2 (2B)
unnamed: IC3.5 (QF), R3.3 (3B)
unnamed: IC3.4 (QE), R3.4 (4B)
unnamed: IC3.3 (QD), R3.5 (5B)
unnamed: IC3.2 (QC), R3.6 (6B)
unnamed: IC3.1 (QB), R3.7 (7B)
unnamed: IC3.15 (QA), R3.8 (8B)
unnamed: IC3.7 (QH), R3.1 (1B)
unnamed: IC4.6 (QG), R4.2 (2B)
unnamed: IC4.5 (QF), R4.3 (3B)
unnamed: IC4.4 (QE), R4.4 (4B)
unnamed: IC4.3 (QD), R4.5 (5B)
unnamed: IC4.2 (QC), R4.6 (6B)
unnamed: IC4.1 (QB), R4.7 (7B)
unnamed: IC4.15 (QA), R4.8 (8B)
unnamed: IC4.7 (QH), R4.1 (1B)
unnamed: J3.3, R1.13 (6C)
unnamed: J3.4, R1.14 (5C)
unnamed: J3.5, R1.15 (4C)
unnamed: J3.6, R1.16 (3C)
unnamed: J3.7, R1.17 (2C)
unnamed: J3.8, R1.18 (1C)
unnamed: J4.1, R2.11 (8C)
unnamed: J4.2, R2.12 (7C)
unnamed: J4.3, R2.13 (6C)
unnamed: J4.4, R2.14 (5C)
unnamed: J4.5, R2.15 (4C)
unnamed: J4.6, R2.16 (3C)
unnamed: J4.7, R2.17 (2C)
unnamed: J4.8, R2.18 (1C)
unnamed: J5.1, R3.11 (8C)
unnamed: J5.2, R3.12 (7C)
unnamed: J5.3, R3.13 (6C)
unnamed: J5.4, R3.14 (5C)
unnamed: J5.5, R3.15 (4C)
unnamed: J5.6, R3.16 (3C)
unnamed: J5.7, R3.17 (2C)
unnamed: J5.8, R3.18 (1C)
unnamed: J6.1, R4.11 (8C)
unnamed: J6.2, R4.12 (7C)
unnamed: J6.3, R4.13 (6C)
unnamed: J6.4, R4.14 (5C)
unnamed: J6.5, R4.15 (4C)
unnamed: J6.6, R4.16 (3C)
unnamed: J6.7, R4.17 (2C)
unnamed: J6.8, R4.18 (1C)
unnamed: J1.5, J2.5, J7.5
unnamed: I.14 (SER), J1.6
unnamed: I.9 (QH*), IC2.14 (SER)
unnamed: IC2.9 (QH*), IC3.14 (SER)
unnamed: IC3.9 (QH*), IC4.14 (SER)
unnamed: IC4.9 (QH*), J2.6, J7.6
unnamed: I.11 (SCK), IC2.11 (SCK), IC3.11 (SCK), IC4.11 (SCK), J1.7, J1.8, J2.7, J2.8, J7.7, J7.8
unnamed: I.12 (RCK), IC2.12 (RCK), IC3.12 (RCK), IC4.12 (RCK), J1.10, J2.10, J7.10
unnamed: J1.9, J2.9, J7.9
unnamed: R1.9 (GND), SJ1.2
unnamed: R1.10 (C), SJ5.2
unnamed: R2.10 (C), SJ6.2
unnamed: R2.9 (GND), SJ2.2
unnamed: R3.9 (GND), SJ3.2
unnamed: R3.10 (C), SJ7.2
unnamed: R4.10 (C), SJ8.2
unnamed: R4.9 (GND), SJ4.2
